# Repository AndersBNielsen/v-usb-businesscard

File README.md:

# ATTiny84 V-USB Business card

Read the full description here: https://abnielsen.com/2018/10/02/business-card-rf24-ws2812b-attiny84-usb/

This project contains KiCad schematics and board layouts, modified versions of the RF24 nRF24L01+ library (https://github.com/nRF24/RF24) and Adafruit's TrinketHidCombo library (https://github.com/adafruit/Adafruit-Trinket-USB/tree/master/TrinketHidCombo) to work with the ATTiny84 with a 16mhz crystal. 

The TrinketHidCombo needed to be reconfigured for the different registers on the T84 compared to the T85 and the RF24 library needed to be made compatible with clockwise pin definitions(a la damellis core).

The microusb connector footprint used is a modified version of one found in Sparkfun's KiCAD connector library. Thanks! (https://github.com/sparkfun/SparkFun-KiCad-Libraries) 

## So what does it do?
It's my business card. It also doubles as a development board. It successfully fits code to accept commands wirelessly to control onboard(or external) WS2812B LEDs and send Play/Pause/Vol up/Vol down/Stop media keys via USB, into the 8192 bytes available on an ATTiny84. Hardware for sending the RF commands is not covered by this project. 

Update: It now also works as a USBasp programmer! (https://github.com/AndersBNielsen/USBasp-t)

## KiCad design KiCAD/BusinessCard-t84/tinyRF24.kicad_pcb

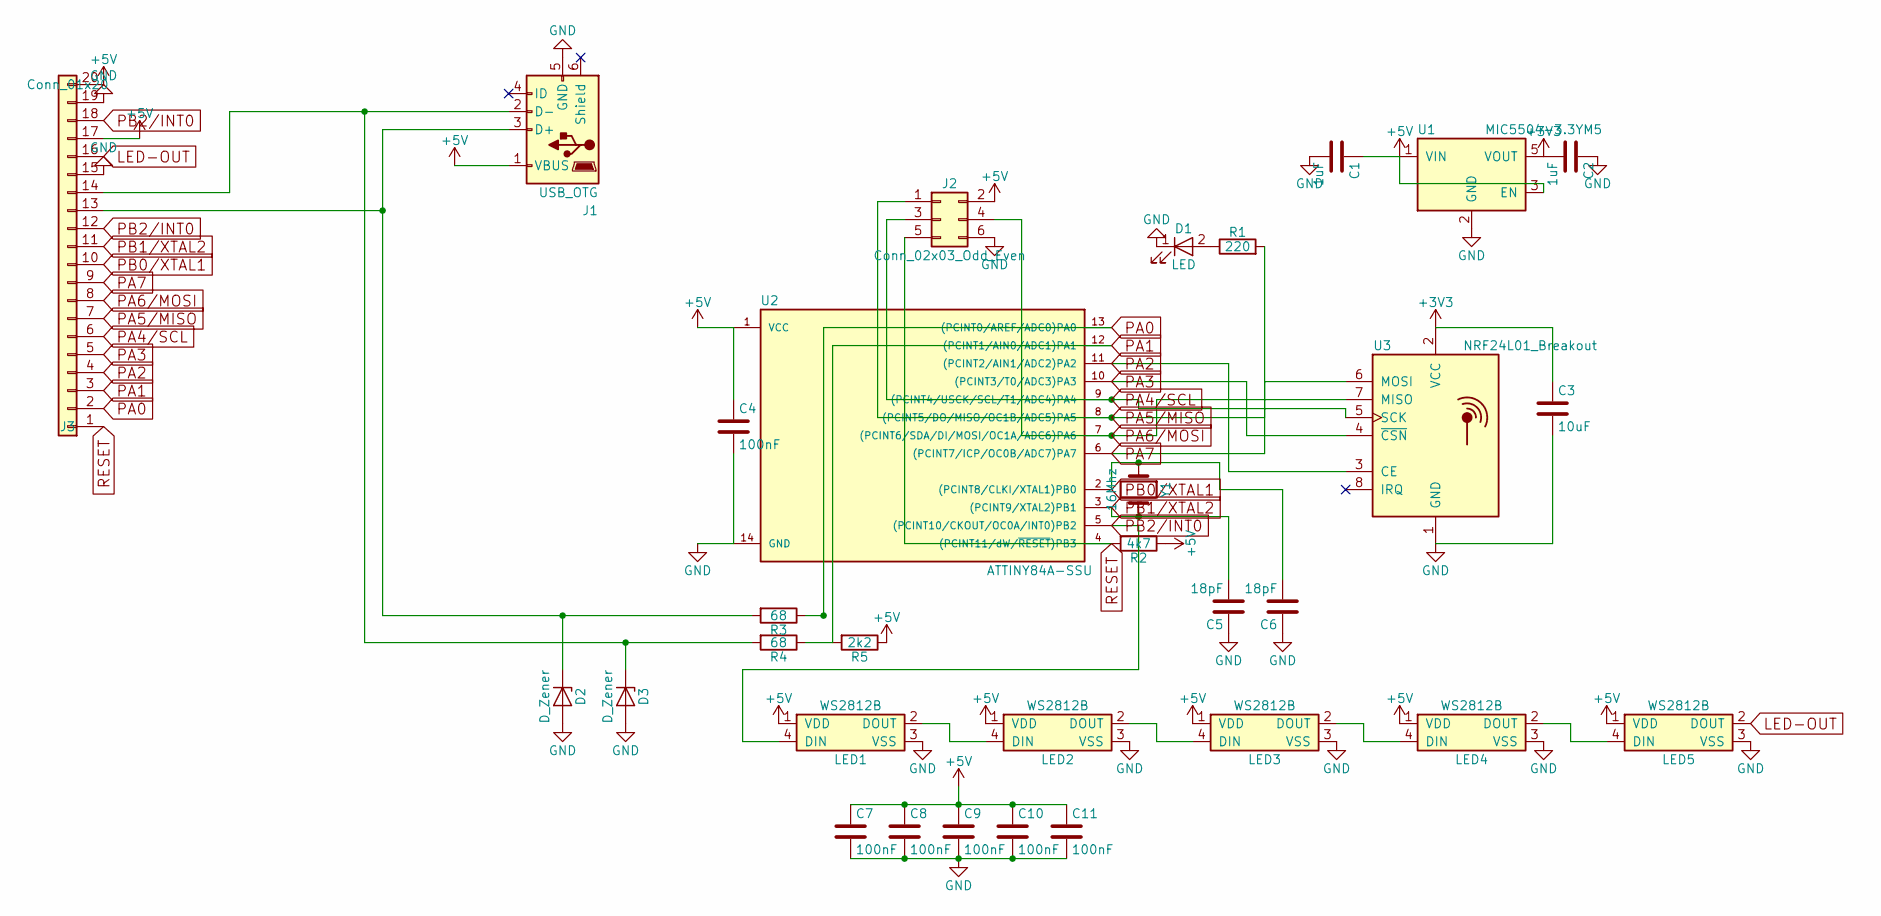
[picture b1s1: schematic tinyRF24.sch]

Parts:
C1, C2: 1uF; C_0603_HandSoldering
C3: 10uF; C_0805_HandSoldering
C4, C7, C8, C9, C10, C11: 100nF; C_0603_HandSoldering
C5, C6: 18pF; C_0603_HandSoldering
D1: LED; LED_0603_HandSoldering
D2, D3: D_Zener; D_SOD-323
J1: USB_OTG; USB-B-MICRO-SMD_V03-fixed
J2: Conn_02x03_Odd_Even; Pin_Header_Straight_2x03_Pitch2.54mm_SMD
J3: Conn_01x20; Pin_Header_Straight_1x20_Pitch2.54mm
LED1, LED2, LED3, LED4, LED5: WS2812B; LED_WS2812B-PLCC4
R1: 220; R_0603_HandSoldering
R2: 4k7; R_0603_HandSoldering
R3, R4: 68; R_0603_HandSoldering
R5: 2k2; R_0603_HandSoldering
U1: MIC5504-3.3YM5; SOT-23-5
U2: ATTINY84A-SSU; SOIC-14_3.9x8.7mm_Pitch1.27mm
U3: NRF24L01_Breakout; NRF24L01-SMD
Y1: 16Mhz; Crystal_HC49-4H_Vertical

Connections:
+3V3: C2.2, C3.1, U1.5 (VOUT), U3.2 (VCC)
+5V: C1.1, C4.1, C7.1, C8.1, C9.1, C10.1, C11.1, J1.1 (VBUS), J2.2, J3.17, J3.20, LED1.1 (VDD), LED2.1 (VDD), LED3.1 (VDD), LED4.1 (VDD), LED5.1 (VDD), R2.1, R5.1, U1.1 (VIN), U1.3 (EN), U2.1 (VCC)
GND: C1.2, C2.1, C3.2, C4.2, C5.1, C6.1, C7.2, C8.2, C9.2, C10.2, C11.2, D1.1 (K), D2.2 (A), D3.2 (A), J1.5 (GND), J2.6, J3.15, J3.19, LED1.3 (VSS), LED2.3 (VSS), LED3.3 (VSS), LED4.3 (VSS), LED5.3 (VSS), U1.2 (GND), U2.14 (GND), U3.1 (GND)
LED-OUT: J3.16, LED5.2 (DOUT)
unnamed: D1.2 (A), R1.1
unnamed: D2.1 (K), J1.3 (D+), J3.13, R3.2
unnamed: D3.1 (K), J1.2 (D-), J3.14, R4.2
unnamed: LED1.2 (DOUT), LED2.4 (DIN)
unnamed: LED2.2 (DOUT), LED3.4 (DIN)
unnamed: LED3.2 (DOUT), LED4.4 (DIN)
unnamed: LED4.2 (DOUT), LED5.4 (DIN)
PA0: J3.2, R3.1, U2.13 ((PCINT0/AREF/ADC0)PA0)
PA1: J3.3, R4.1, R5.2, U2.12 ((PCINT1/AIN0/ADC1)PA1)
PA2: J3.4, U2.11 ((PCINT2/AIN1/ADC2)PA2), U3.3 (CE)
PA3: J3.5, U2.10 ((PCINT3/T0/ADC3)PA3), U3.4 (~CSN)
PA4/SCL: J2.3, J3.6, U2.9 ((PCINT4/USCK/SCL/T1/ADC4)PA4), U3.5 (SCK)
PA5/MISO: J2.1, J3.7, U2.8 ((PCINT5/DO/MISO/OC1B/ADC5)PA5), U3.6 (MOSI)
PA6/MOSI: J2.4, J3.8, U2.7 ((PCINT6/SDA/DI/MOSI/OC1A/ADC6)PA6), U3.7 (MISO)
PA7: J3.9, R1.2, U2.6 ((PCINT7/ICP/OC0B/ADC7)PA7)
PB0/XTAL1: C6.2, J3.10, U2.2 ((PCINT8/CLKI/XTAL1)PB0), Y1.1
PB1/XTAL2: C5.2, J3.11, U2.3 ((PCINT9/XTAL2)PB1), Y1.2
PB2/INT0: J3.12, J3.18, LED1.4 (DIN), U2.5 ((PCINT10/CKOUT/OC0A/INT0)PB2)
RESET: J2.5, J3.1, R2.2, U2.4 ((PCINT11/dW/~RESET~)PB3)

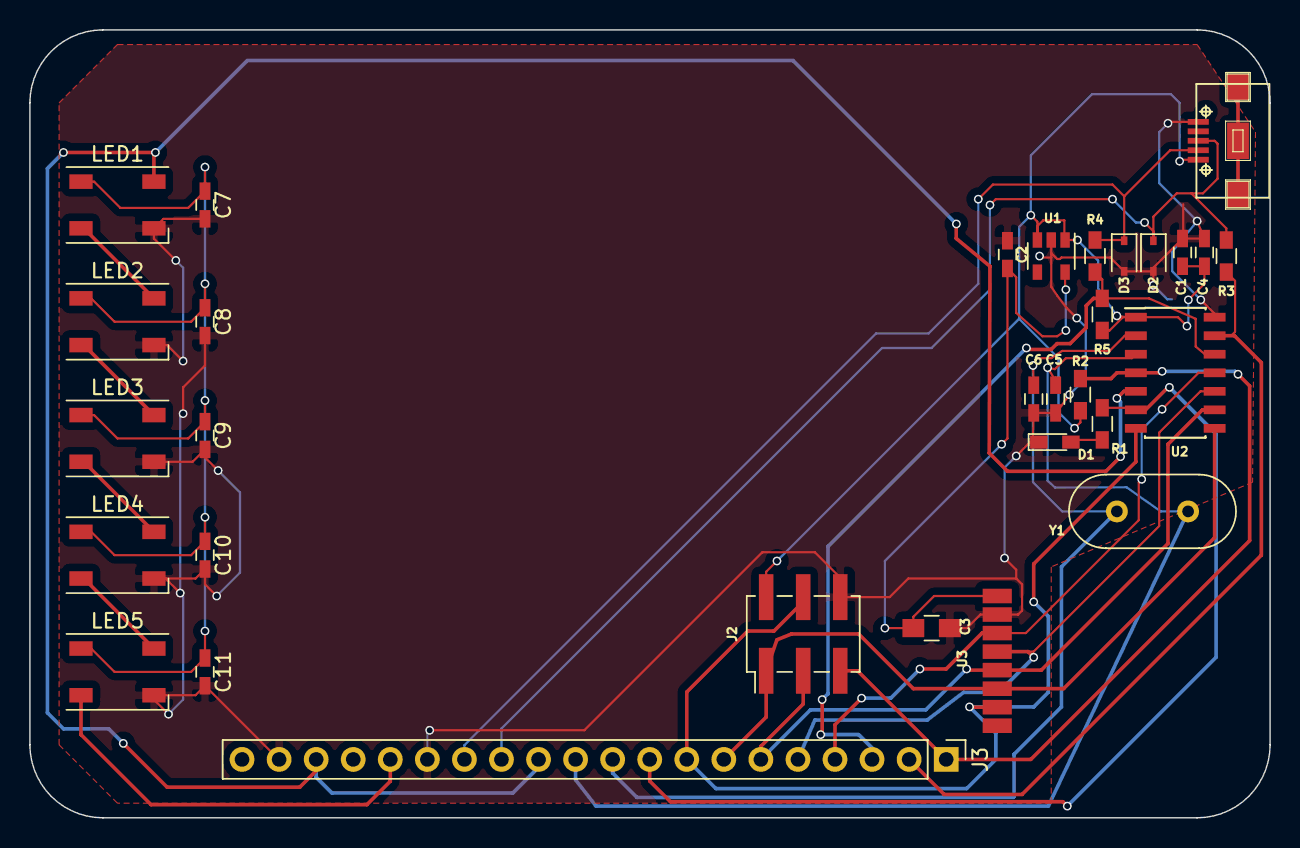
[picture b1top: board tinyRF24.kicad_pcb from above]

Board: 2 copper layers, 85.0 x 54.0 mm, 31 parts (0 on the bottom side), 23 nets.

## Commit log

2018-10-04 Add files via upload
    Arduino sketch
